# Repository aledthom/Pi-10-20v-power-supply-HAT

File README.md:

# pipoweruhat

Power supply hat 10-20v

Main version including i2c RTC

version using RTC without seperate oscillator

version without RTC (same pcb layout)

version for single layer etching with less drilling.

TODO-
Add icsp jumpers
add reset switch jumpers
add config for shutdown time on non rtc versions

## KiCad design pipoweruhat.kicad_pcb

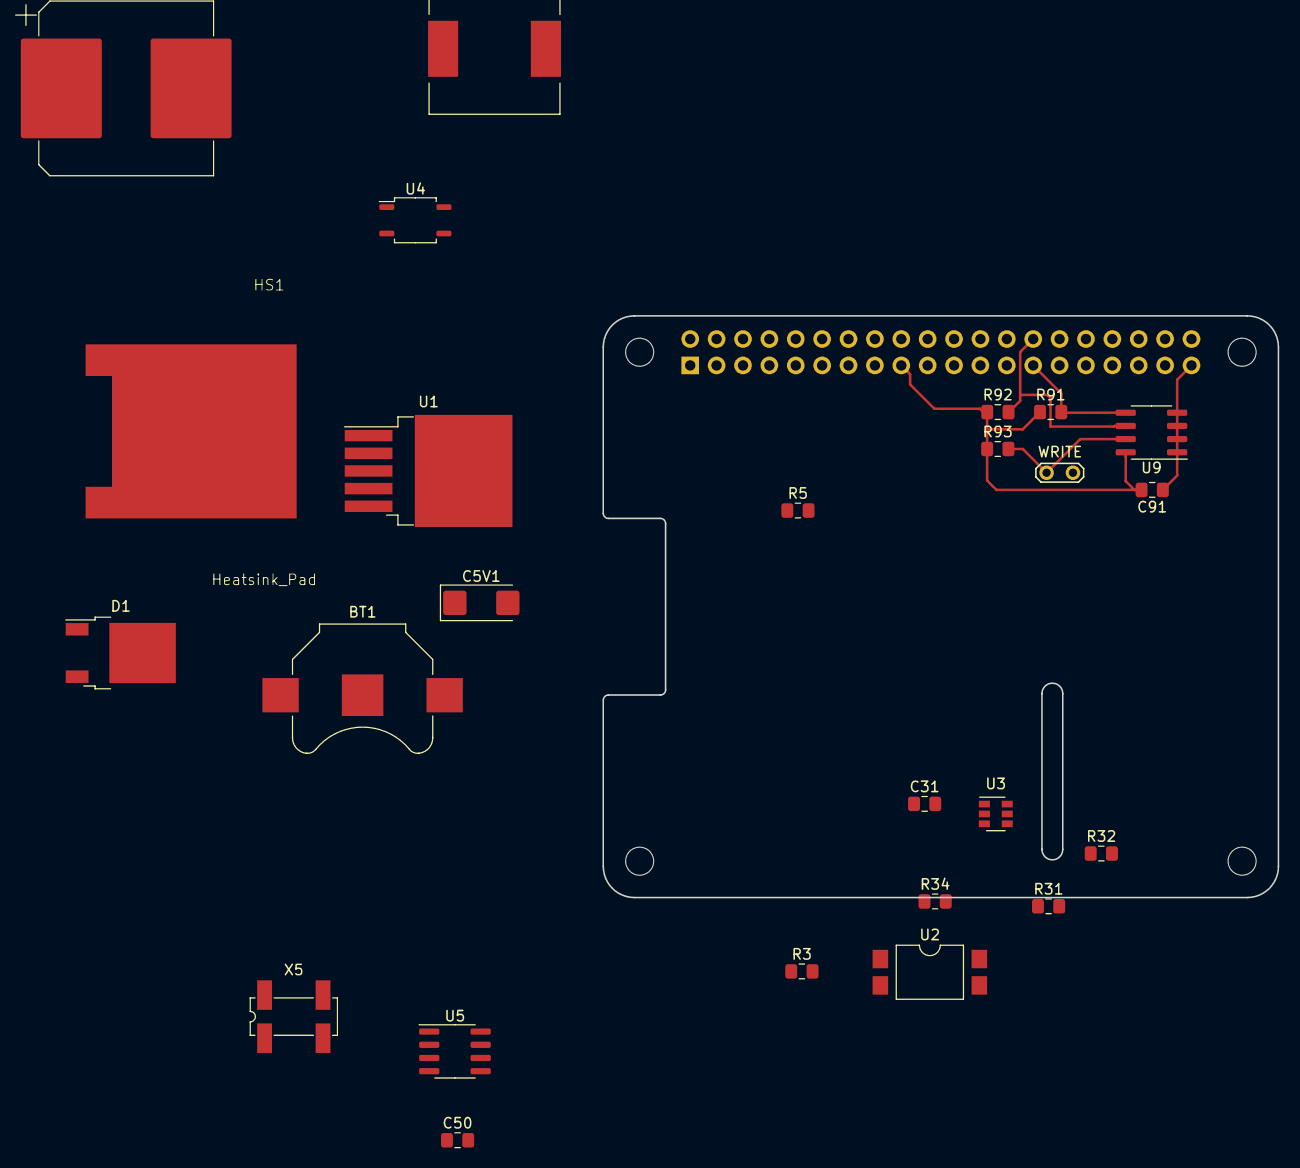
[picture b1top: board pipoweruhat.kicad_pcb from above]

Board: 2 copper layers, 65.0 x 56.0 mm, 30 parts (1 on the bottom side), 20 nets.

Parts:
BT1: Battery_Cell; BatteryHolder_Keystone_3000_1x12mm
C5V1: 220uF; CP_EIA-6032-20_AVX-F_Pad2.25x2.35mm_HandSolder
C12V1: 680uF; CP_Elec_16x17.5
C31, C50, C91: 100n; C_0805_2012Metric_Pad1.15x1.40mm_HandSolder
D1: 50WQ03; TO-252-2
H1, H2, H3, H4: MountingHole; MountingHole_2.7mm_M2.5_uHAT_RPi
HS1: Heatsink_Pad; HSINK_7109DG
J1: GPIO_CONNECTOR; PinSocket_2x20_P2.54mm_Vertical_Centered_Anchor
L1: 33mH; L_12x12mm_H6mm
R3: 660R; R_0805_2012Metric_Pad1.15x1.40mm_HandSolder
R5: R; R_0805_2012Metric_Pad1.15x1.40mm_HandSolder
R31, R32, R34: 10k; R_0805_2012Metric_Pad1.15x1.40mm_HandSolder
R91, R92: 3.9k; R_0805_2012Metric_Pad1.15x1.40mm_HandSolder
R93: 1k; R_0805_2012Metric_Pad1.15x1.40mm_HandSolder
U1: LM2596S-5; TO-263-5_TabPin3
U2: SFH6156-2T; SMDIP-4_W9.53mm_Clearance8mm
U3: PIC10F200-IOT; SOT-23-6
U4: CPC1017N; SOP-4_3.8x4.1mm_P2.54mm
U5: DS1307Z+; SOIC-8_3.9x4.9mm_P1.27mm
U9: CAT24C32WI; SOIC-8_3.9x4.9mm_P1.27mm
WRITE: TestPoint_2Pole; TestPoint_2Pads_Pitch2.54mm_Drill0.8mm
X5: MC-306; Crystal_SMD_SeikoEpson_MC306-4Pin_8.0x3.2mm_HandSoldering

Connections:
+3V3: C31.1, C50.1, J1.1, R31.1, R32.1, R34.1, U3.5, U5.8
+5V: C5V1.1, J1.2, L1.1, U1.4
+VSW: C12V1.1, U1.1, U4.3
/+3.3v: C91.2, J1.17, R91.1, R92.1, R93.1, U9.8
/Clock_to_PIC_GPIO_0: R32.2, U3.1, U5.7
/GPIO2_SDA1: J1.3, U5.5
/GPIO3_SCL1: J1.5, U5.6
/GPIO4_GPIO_GCLK: J1.7, R34.2, U3.6
/ID_SCL: J1.28, R92.2, U9.6
/ID_SDA: J1.27, R91.2, U9.5
GND: BT1.2, C5V1.2, C12V1.2, C31.2, C50.2, C91.1, D1.1, D1.3, HS1.1, J1.6, J1.39, U1.3, U1.5, U2.2, U2.3, U3.2, U4.2, U5.4, U9.1, U9.2, U9.3, U9.4, WRITE.2
unnamed: BT1.1, U5.3
unnamed: D1.2, L1.2, U1.2
unnamed: R3.2, U2.1
unnamed: R5.1, U4.1
unnamed: R5.2, U3.4
unnamed: R31.2, U2.4, U3.3
unnamed: R93.2, U9.7, WRITE.1
unnamed: U5.1, X5.2
unnamed: U5.2, X5.1

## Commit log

2019-10-28 schematic done
    footprints assigned for tht parts
